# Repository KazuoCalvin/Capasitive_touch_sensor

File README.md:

# Design and implement a capacitive touch sensor-activated light stand.
## 1. Project scope
- Implement 3 MHz square wave signal generator using 555
- Design and implement capacitive touch sensor without micro controller
- Implement 120V power, step down to 5V for powering lower voltage section of board
- Using 120V to power light bulb, control on-off with a relay.
- Design circuit so that touch sensor latches on-off correctly.

## 2. Key Design Choices

## 3. Project progress
- 10/19/2024  verified capacitive touch sensor concept works with breadboard prototype.
- 10/31/2024  added schematics for 3MHz gen, and capacitive touch sensor.

## 4. Components
Follow the following format: 

Name, value, DigiKey link, number needed

- 555 timer

LMC555CN/NOPB, , https://www.digikey.ca/en/products/detail/texas-instruments/LMC555CN-NOPB/32623, bought

- Capacitor

, 1nF, 
GRM033R71A103KA01D, 10nF, https://www.digikey.ca/en/products/detail/murata-electronics/GRM033R71A103KA01D/702460

- Inverter

SN74LVC1G14DBVR, , https://www.digikey.ca/en/products/detail/texas-instruments/SN74LVC1G14DBVR/385724

- Potentiometer

N6S25T0C-103-3030, 10kO, https://www.digikey.ca/en/products/detail/amphenol-piher-sensing-systems/N6S25T0C-103-3030/13244337

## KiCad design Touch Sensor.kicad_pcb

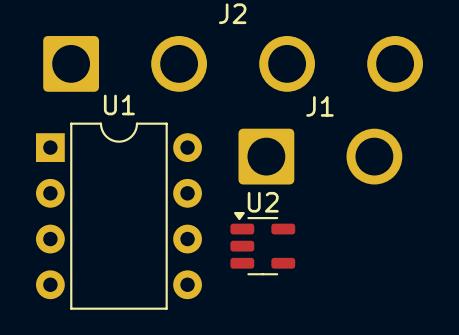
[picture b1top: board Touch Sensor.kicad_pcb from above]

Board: 2 copper layers, 4 parts (0 on the bottom side), 6 nets, no tracks yet.

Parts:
J1: Conn_01x02_Pin; SolderWire-1.5sqmm_1x02_P6mm_D1.7mm_OD3mm
J2: Conn_01x04_Pin; SolderWire-1.5sqmm_1x04_P6mm_D1.7mm_OD3mm
U1: LMC555xN; DIP-8_W7.62mm
U2: SN74LVC1G14DBV; SOT-23-5

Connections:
GND: U1.1 (GND), U2.3 (GND)
unnamed: J1.1, U1.4 (R), U1.8 (VCC)
unnamed: J1.2, U1.3 (Q)
unnamed: J2.1, U2.5 (VCC)
unnamed: J2.4, U2.4
unnamed: U1.2 (TR), U1.6 (THR)

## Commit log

2024-10-28 pcb init
2024-10-28 - test commit from KiCad
2024-10-31 added 3MHz gen and touch sensor circuit
2024-10-31 modified touch circuit
2024-10-31 update component list on readme
2024-11-02 added components to readme
2024-11-08 changed schematic hierarchy
